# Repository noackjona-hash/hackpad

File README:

In this Repo you can find my Version of the Hack Deck. More infos comming soon.

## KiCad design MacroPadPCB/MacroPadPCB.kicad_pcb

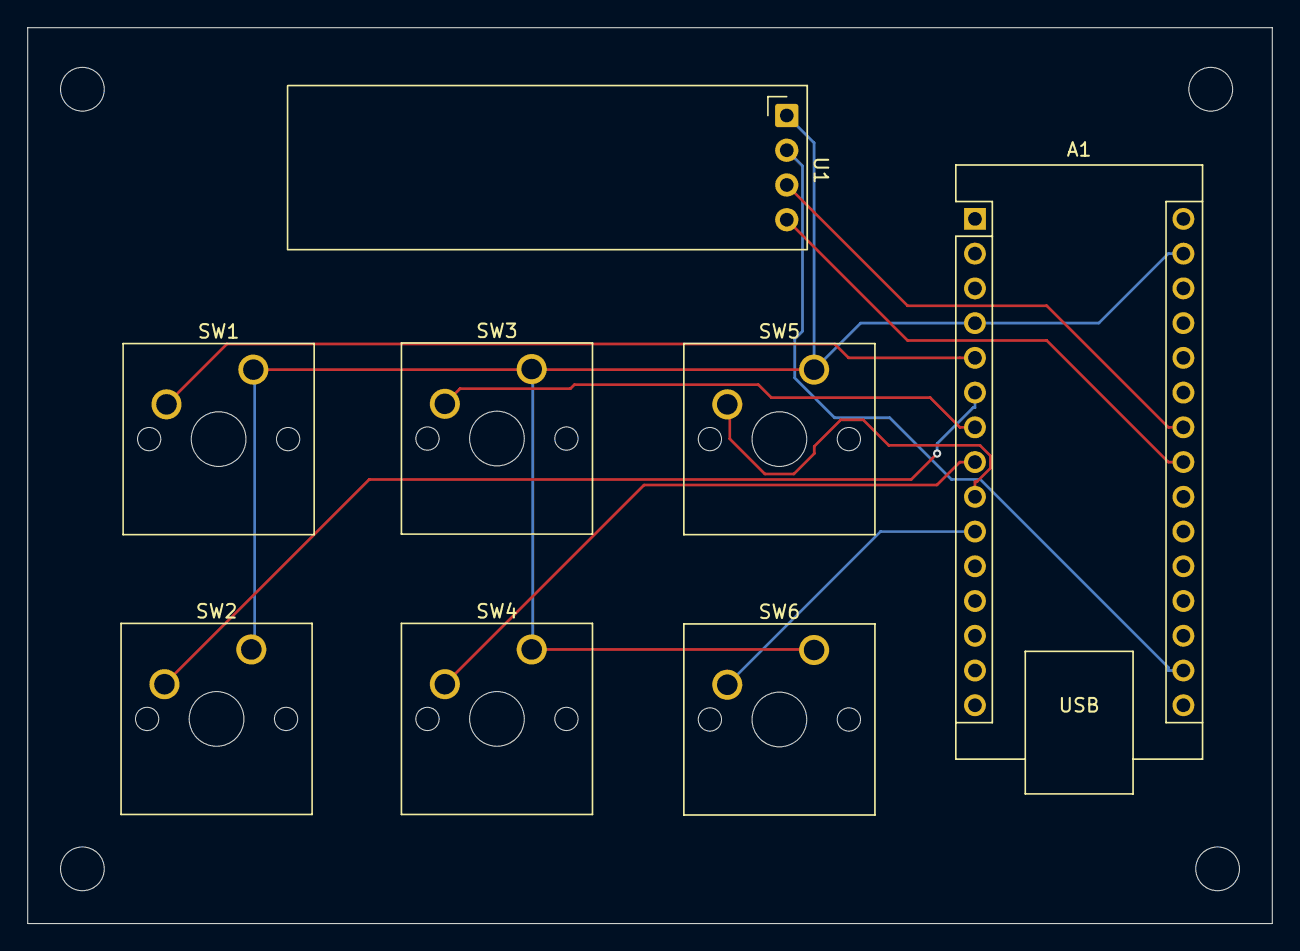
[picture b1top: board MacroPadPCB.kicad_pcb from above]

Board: 2 copper layers, 91.0 x 65.5 mm, 12 parts (0 on the bottom side), 10 nets.

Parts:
A1: Arduino_Nano_RP2040_Connect; Arduino_Nano
H4, H5, H6, H7: MountingHole_Pad_MP; MountingHole_3.2mm_M3
SW1, SW2, SW3, SW4, SW5, SW6: SW_Push; SW_Cherry_MX_1.00u_PCB
U1: ER_OLEDM0.91_1x-I2C

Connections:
+3.3V: A1.17 (3V3), U1.2 (VCC)
GND: A1.4 (GND), A1.29 (GND), SW1.1, SW2.1, SW3.1, SW4.1, SW5.1, SW6.1, U1.1 (GND)
unnamed: A1.5 (D2), SW1.2
unnamed: A1.6 (D3), SW2.2
unnamed: A1.7 (D4), SW3.2
unnamed: A1.8 (D5), SW4.2
unnamed: A1.9 (D6), SW5.2
unnamed: A1.10 (D7), SW6.2
unnamed: A1.24 (SCL/A5), U1.3 (SCL)
unnamed: A1.23 (SDA/A4), U1.4 (SDA)
